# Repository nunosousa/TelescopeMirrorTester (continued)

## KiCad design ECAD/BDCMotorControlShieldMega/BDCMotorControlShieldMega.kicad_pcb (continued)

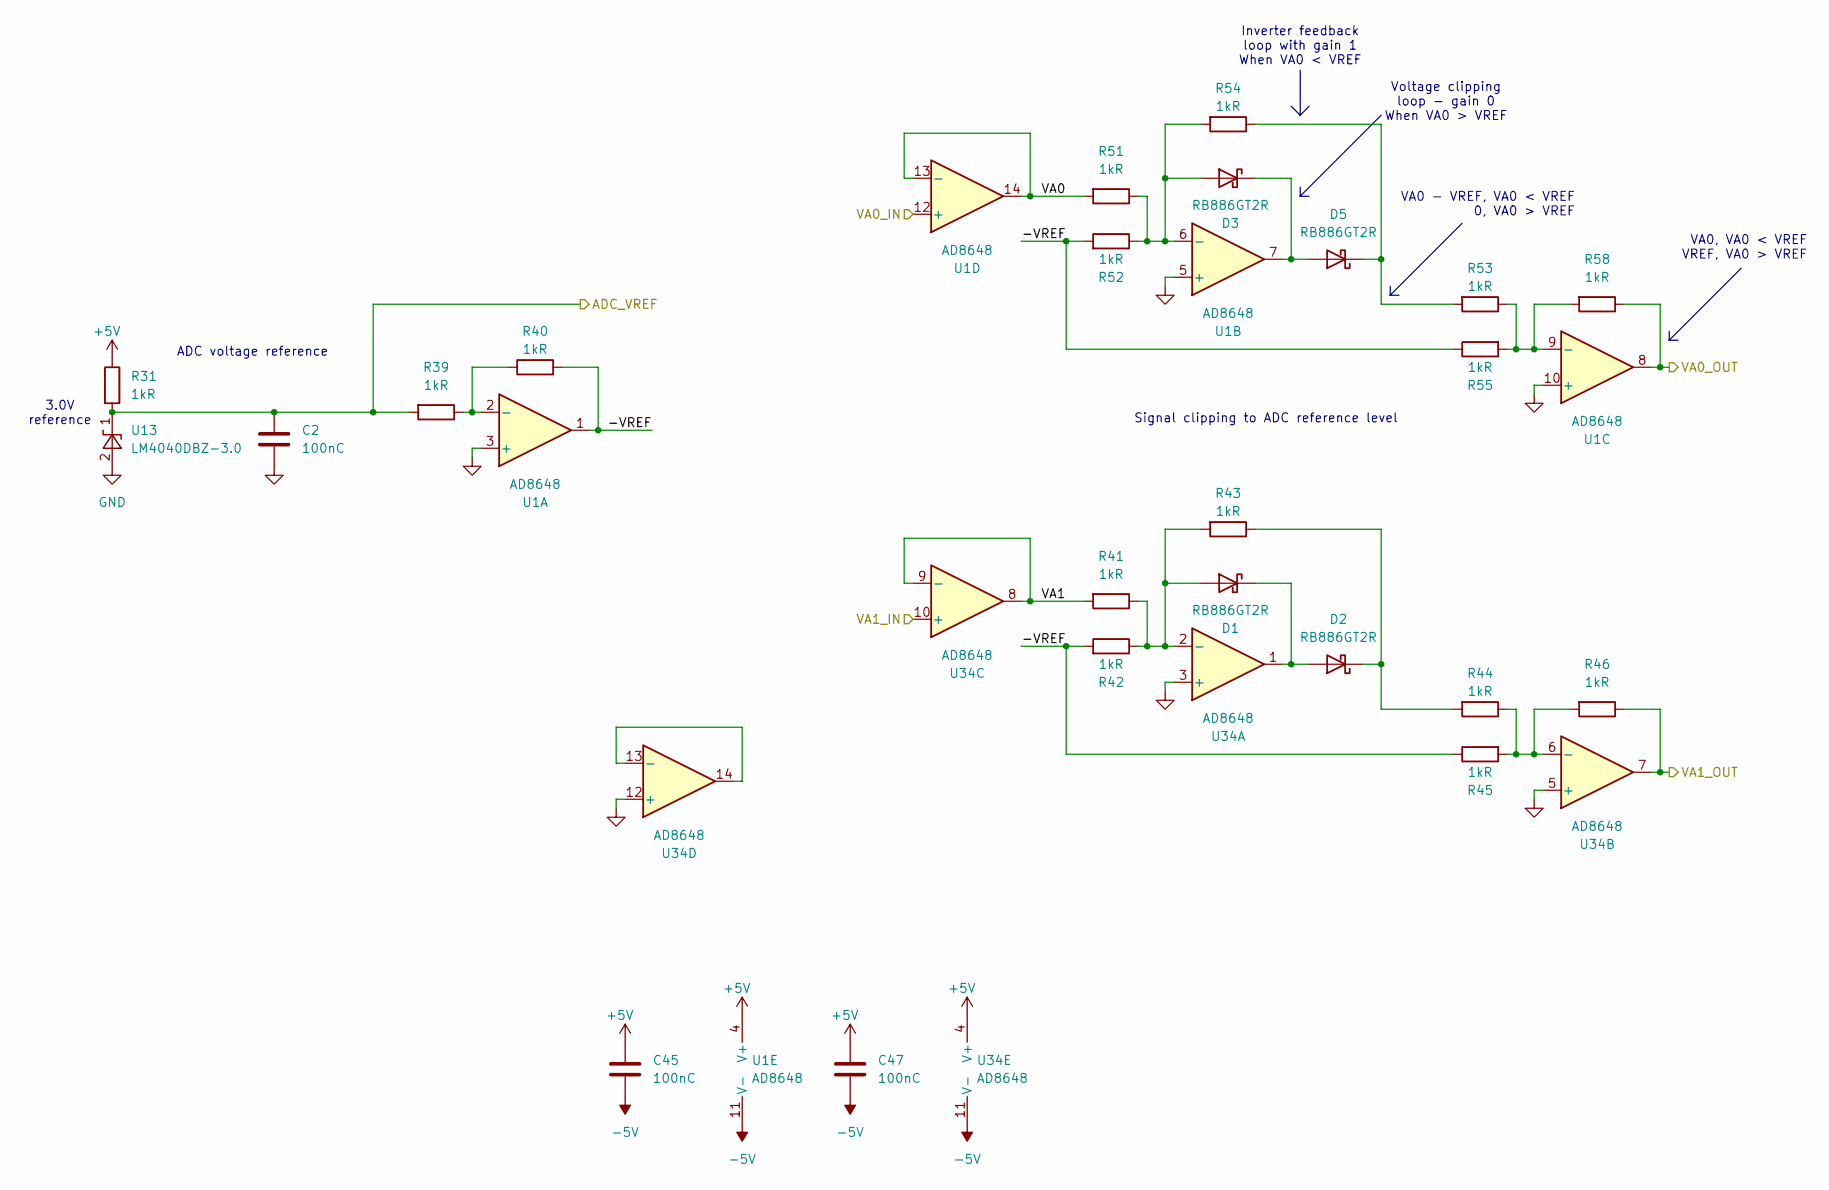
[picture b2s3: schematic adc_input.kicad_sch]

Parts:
C2, C45, C47: 100nC; C_0805_2012Metric
D1, D2, D3, D5: RB886GT2R; MPN RB886GT2R
R31: 1kR; R_0805_2012Metric; MPN AC0805FR-7W1KL
R39, R40, R41, R42, R43, R44, R45, R46, R51, R52, R53, R54, R55, R58: 1kR; R_0805_2012Metric
U1, U34: AD8648; TSSOP-14_4.4x5mm_P0.65mm; MPN AD8648ARUZ
U13: LM4040DBZ-3.0; SOT-23; MPN LM4040B30IDBZR

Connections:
+5V: C45.1, C47.1, R31.1, U1.4 (V+), U34.4 (V+); also elsewhere on the board
-5V: C45.2, C47.2, U1.11 (V-), U34.11 (V-); also elsewhere on the board
/A0: R58.1, U1.8; also elsewhere on the board
/A1: R46.1, U34.7; also elsewhere on the board
/ADC conditioning/-VREF: R40.2, R42.2, R45.1, R52.2, R55.1, U1.1
/ADC conditioning/VA0: R51.2, U1.13 (-), U1.14
/ADC conditioning/VA0_IN: U1.12 (+); also elsewhere on the board
/ADC conditioning/VA1: R41.2, U34.8, U34.9 (-)
/ADC conditioning/VA1_IN: U34.10 (+); also elsewhere on the board
/AREF: C2.1, R31.2, R39.2, U13.1 (K); also elsewhere on the board
GND: C2.2, U1.3 (+), U1.5 (+), U1.10 (+), U13.2 (A), U34.3 (+), U34.5 (+), U34.12 (+); also elsewhere on the board
unnamed: D1.2 (A), R41.1, R42.1, R43.2, U34.2 (-)
unnamed: D1.1 (K), D2.2 (A), U34.1
unnamed: D2.1 (K), R43.1, R44.2
unnamed: D3.2 (A), R51.1, R52.1, R54.2, U1.6 (-)
unnamed: D3.1 (K), D5.2 (A), U1.7
unnamed: D5.1 (K), R53.2, R54.1
unnamed: R39.1, R40.1, U1.2 (-)
unnamed: R53.1, R55.2, R58.2, U1.9 (-)
unnamed: R44.1, R45.2, R46.2, U34.6 (-)
unnamed: U34.13 (-), U34.14

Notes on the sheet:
Inverter feedback loop with gain 1 When VA0 < VREF
3.0V reference
ADC voltage reference
Signal clipping to ADC reference level
Voltage clipping loop - gain 0 When VA0 > VREF
VA0, VA0 < VREF VREF, VA0 > VREF
VA0 - VREF, VA0 < VREF 0, VA0 > VREF

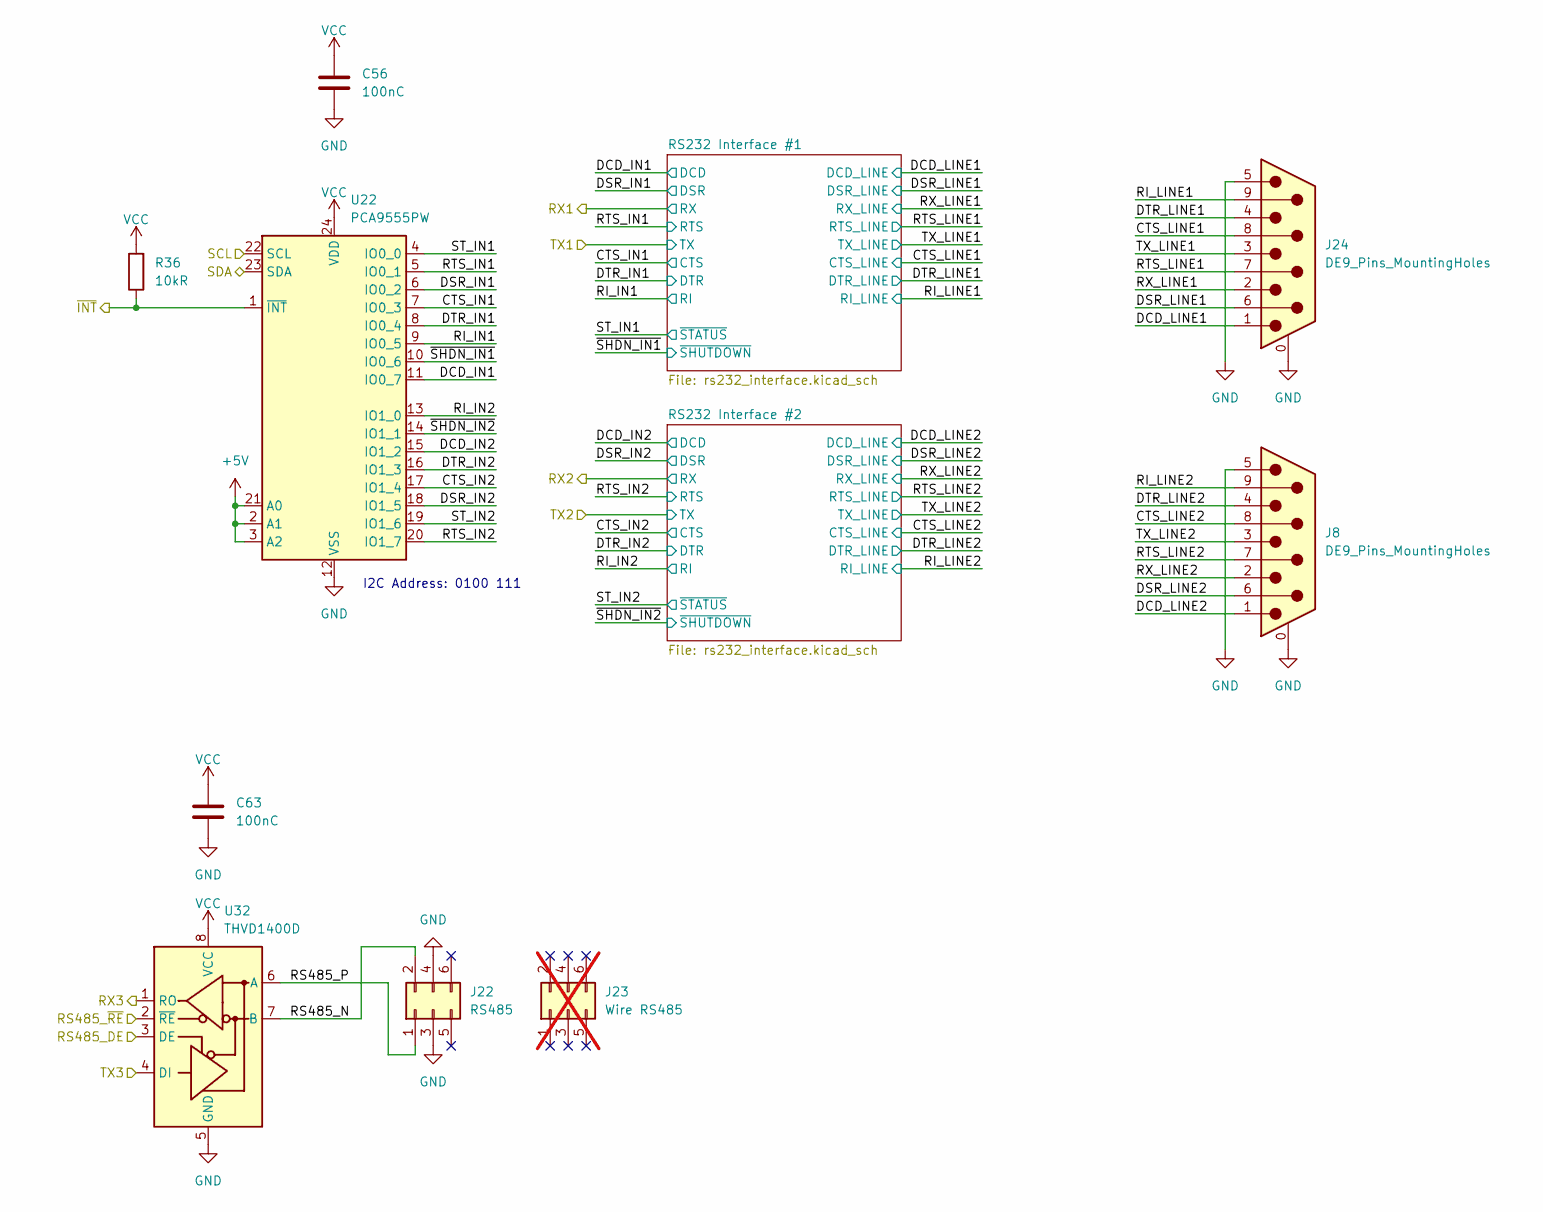
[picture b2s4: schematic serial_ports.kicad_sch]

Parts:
C56, C63: 100nC; C_0805_2012Metric
J8, J24: DE9_Pins_MountingHoles; DSUB-9_Pins_Vertical_P2.77x2.84mm_MountingHoles
J22: RS485; IDC-Header_2x03_P2.54mm_Vertical; MPN HC-JN254-2-03-Z
J23: Wire RS485; IDC-Header_2x03_P2.54mm_Vertical; MPN I254-2*3-G-3-B; not fitted
R36: 10kR; R_0805_2012Metric; MPN RC0805JR-0710KL
U22: PCA9555PW; TSSOP-24_4.4x7.8mm_P0.65mm; MPN PCA9555PW,118
U32: THVD1400D; SOIC-8_3.9x4.9mm_P1.27mm; MPN THVD1400DR

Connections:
+5V: U22.2 (A1), U22.3 (A2), U22.21 (A0); also elsewhere on the board
/*2: U32.2 (~RE); also elsewhere on the board
/*3: U32.3 (DE); also elsewhere on the board
/RX3/15: U32.1 (RO); also elsewhere on the board
/SCL/21: U22.22 (SCL); also elsewhere on the board
/SDA/20: U22.23 (SDA); also elsewhere on the board
/Serial ports/CTS_IN1: U22.7 (IO0_3); also elsewhere on the board
/Serial ports/CTS_IN2: U22.17 (IO1_4); also elsewhere on the board
/Serial ports/CTS_LINE1: J24.8; also elsewhere on the board
/Serial ports/CTS_LINE2: J8.8; also elsewhere on the board
/Serial ports/DCD_IN1: U22.11 (IO0_7); also elsewhere on the board
/Serial ports/DCD_IN2: U22.15 (IO1_2); also elsewhere on the board
/Serial ports/DCD_LINE1: J24.1; also elsewhere on the board
/Serial ports/DCD_LINE2: J8.1; also elsewhere on the board
/Serial ports/DSR_IN1: U22.6 (IO0_2); also elsewhere on the board
/Serial ports/DSR_IN2: U22.18 (IO1_5); also elsewhere on the board
/Serial ports/DSR_LINE1: J24.6; also elsewhere on the board
/Serial ports/DSR_LINE2: J8.6; also elsewhere on the board
/Serial ports/DTR_IN1: U22.8 (IO0_4); also elsewhere on the board
/Serial ports/DTR_IN2: U22.16 (IO1_3); also elsewhere on the board
/Serial ports/DTR_LINE1: J24.4; also elsewhere on the board
/Serial ports/DTR_LINE2: J8.4; also elsewhere on the board
/Serial ports/RI_IN1: U22.9 (IO0_5); also elsewhere on the board
/Serial ports/RI_IN2: U22.13 (IO1_0); also elsewhere on the board
/Serial ports/RI_LINE1: J24.9; also elsewhere on the board
/Serial ports/RI_LINE2: J8.9; also elsewhere on the board
/Serial ports/RS485_N: J22.2, U32.7 (B)
/Serial ports/RS485_P: J22.1, U32.6 (A)
/Serial ports/RTS_IN1: U22.5 (IO0_1); also elsewhere on the board
/Serial ports/RTS_IN2: U22.20 (IO1_7); also elsewhere on the board
/Serial ports/RTS_LINE1: J24.7; also elsewhere on the board
/Serial ports/RTS_LINE2: J8.7; also elsewhere on the board
/Serial ports/RX_LINE1: J24.2; also elsewhere on the board
/Serial ports/RX_LINE2: J8.2; also elsewhere on the board
/Serial ports/ST_IN1: U22.4 (IO0_0); also elsewhere on the board
/Serial ports/ST_IN2: U22.19 (IO1_6); also elsewhere on the board
/Serial ports/TX_LINE1: J24.3; also elsewhere on the board
/Serial ports/TX_LINE2: J8.3; also elsewhere on the board
/Serial ports/~INT: R36.1, U22.1 (~INT)
/Serial ports/~SHDN_IN1: U22.10 (IO0_6); also elsewhere on the board
/Serial ports/~SHDN_IN2: U22.14 (IO1_1); also elsewhere on the board
/TX3/14: U32.4 (DI); also elsewhere on the board
GND: C56.2, C63.2, J8.0 (PAD), J8.5, J22.3, J22.4, J24.0 (PAD), J24.5, U22.12 (VSS), U32.5 (GND); also elsewhere on the board
VCC: C56.1, C63.1, R36.2, U22.24 (VDD), U32.8 (VCC); also elsewhere on the board

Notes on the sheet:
I2C Address: 0100 111

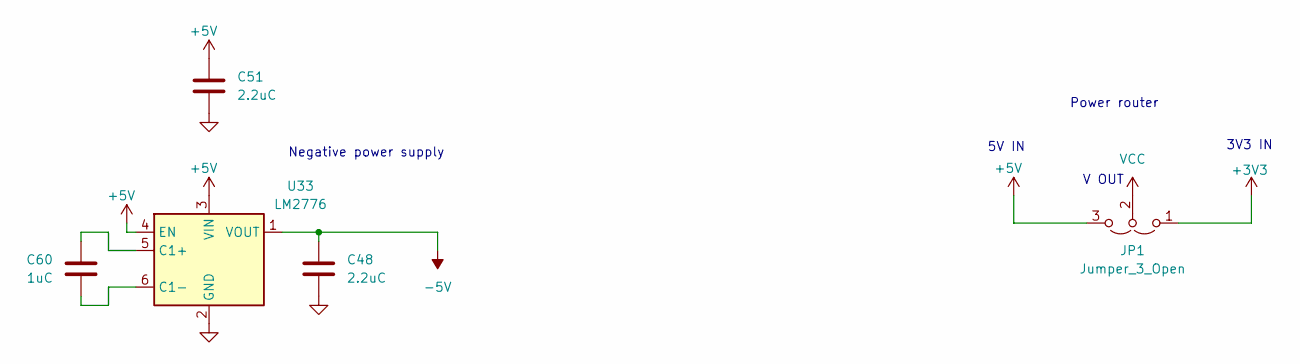
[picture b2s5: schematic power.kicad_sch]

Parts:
C48, C51: 2.2uC; C_0805_2012Metric
C60: 1uC; C_0805_2012Metric
JP1: Jumper_3_Open; PinHeader_1x03_P2.54mm_Vertical
U33: LM2776; SOT-23-6

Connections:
+3V3: JP1.1 (A); also elsewhere on the board
+5V: C51.1, JP1.3 (B), U33.3 (VIN), U33.4 (EN); also elsewhere on the board
-5V: C48.1, U33.1 (VOUT); also elsewhere on the board
GND: C48.2, C51.2, U33.2 (GND); also elsewhere on the board
unnamed: C60.1, U33.5 (C1+)
unnamed: C60.2, U33.6 (C1-)
VCC: JP1.2 (C); also elsewhere on the board

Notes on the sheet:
3V3 IN
Power router
Negative power supply
V OUT
5V IN

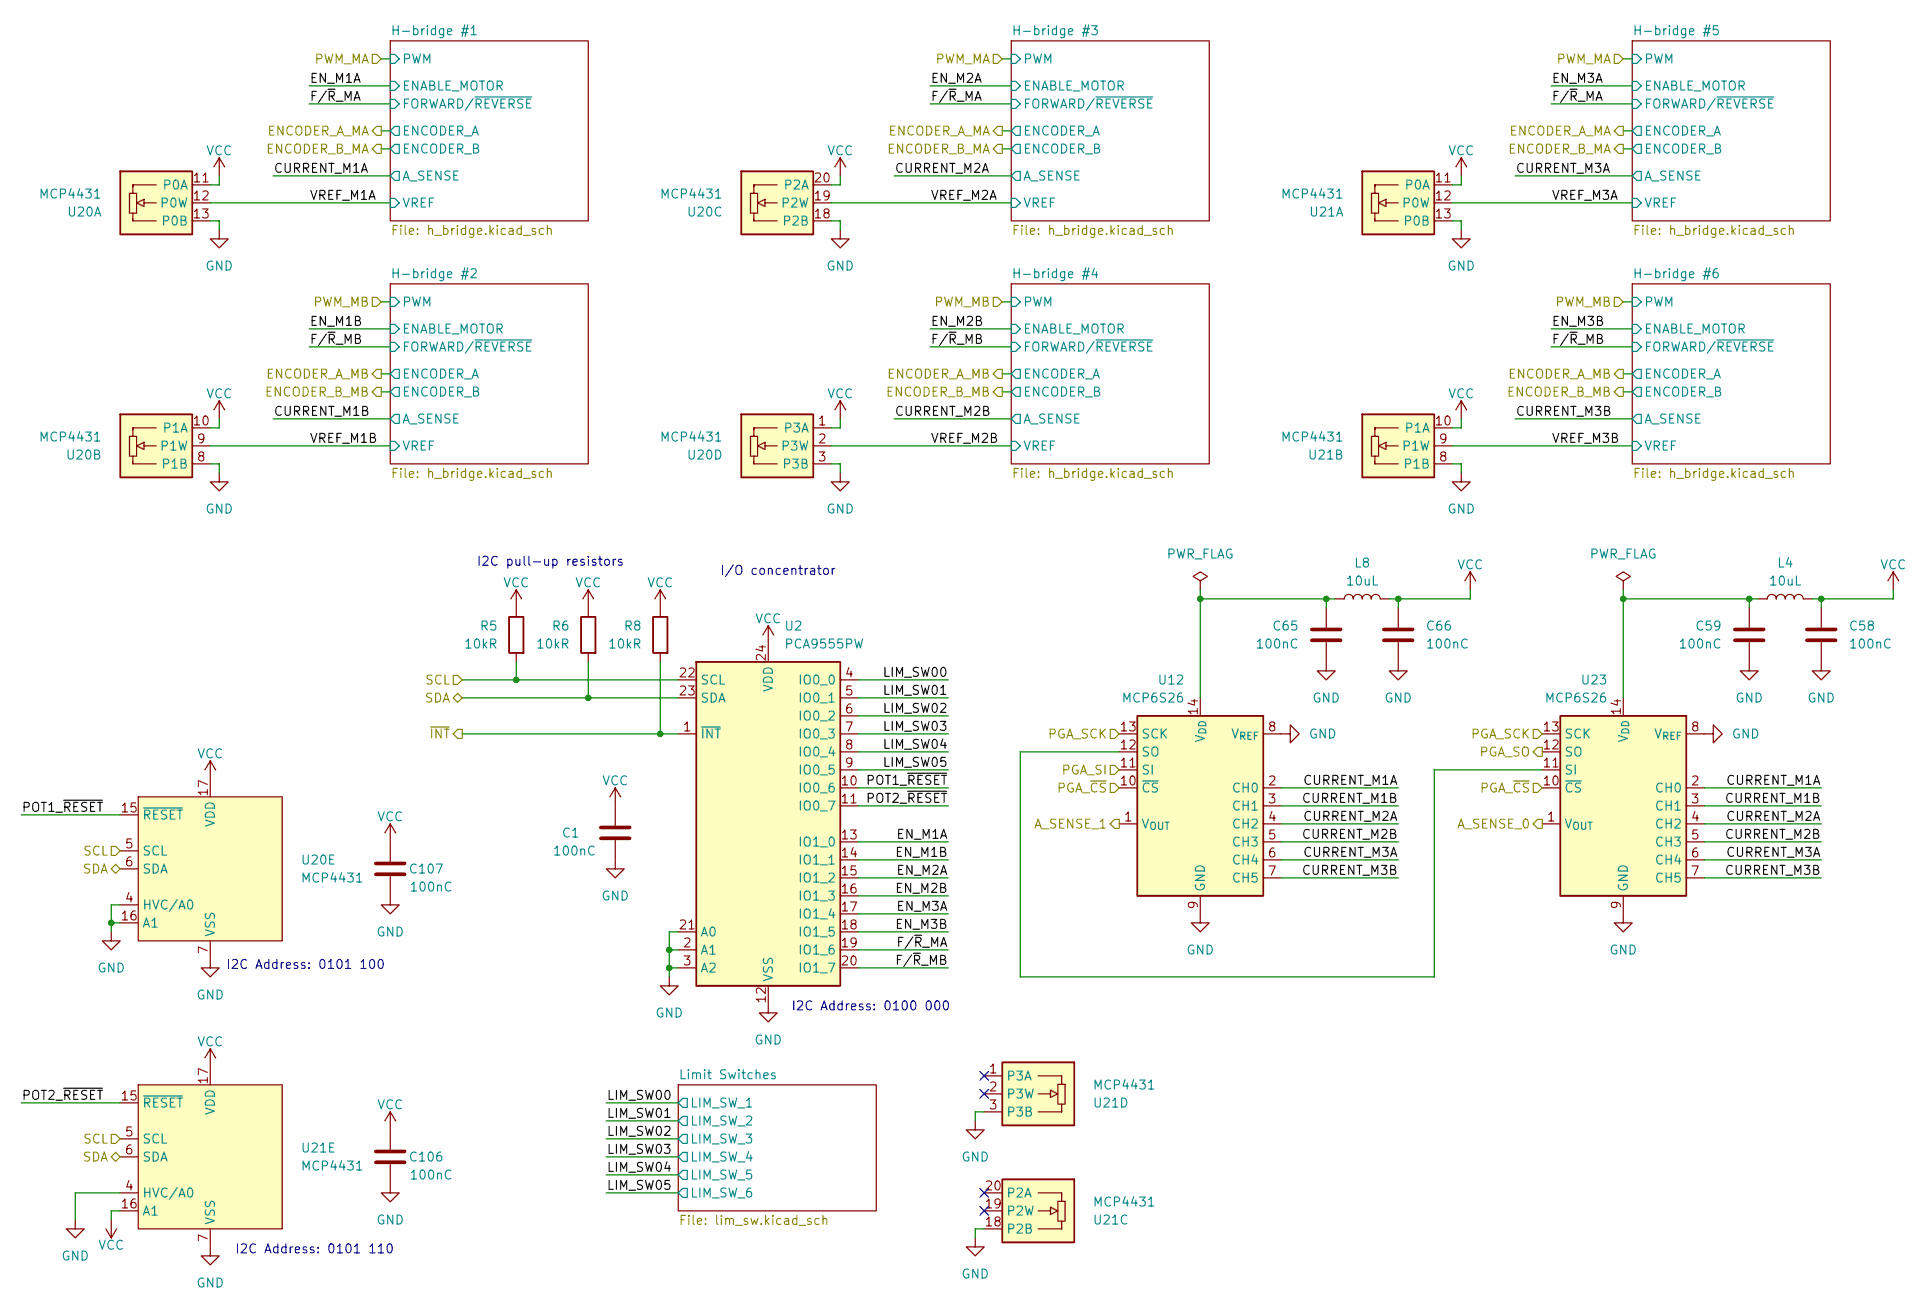
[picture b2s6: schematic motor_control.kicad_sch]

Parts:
C1, C58, C59, C65, C66, C106, C107: 100nC; C_0805_2012Metric
L4, L8: 10uL; L_0805_2012Metric; MPN LQM21FN100M80L
R5, R6, R8: 10kR; R_0805_2012Metric; MPN RC0805JR-0710KL
U2: PCA9555PW; TSSOP-24_4.4x7.8mm_P0.65mm; MPN PCA9555PW,118
U12, U23: MCP6S26; SOIC-14_3.9x8.7mm_P1.27mm; MPN MCP6S26-I/SL
U20, U21: MCP4431; TSSOP-20_4.4x6.5mm_P0.65mm; MPN MCP4431-103E/ST

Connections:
/50: U23.12 (SO); also elsewhere on the board
/51: U12.11 (SI); also elsewhere on the board
/53: U12.10 (~CS), U23.10 (~CS); also elsewhere on the board
/*52: U12.13 (SCK), U23.13 (SCK); also elsewhere on the board
/ADC conditioning/VA0_IN: U23.1 (V_{OUT}); also elsewhere on the board
/ADC conditioning/VA1_IN: U12.1 (V_{OUT}); also elsewhere on the board
/Motor Control/CURRENT_M1A: U12.2 (CH0), U23.2 (CH0); also elsewhere on the board
/Motor Control/CURRENT_M1B: U12.3 (CH1), U23.3 (CH1); also elsewhere on the board
/Motor Control/CURRENT_M2A: U12.4 (CH2), U23.4 (CH2); also elsewhere on the board
/Motor Control/CURRENT_M2B: U12.5 (CH3), U23.5 (CH3); also elsewhere on the board
/Motor Control/CURRENT_M3A: U12.6 (CH4), U23.6 (CH4); also elsewhere on the board
/Motor Control/CURRENT_M3B: U12.7 (CH5), U23.7 (CH5); also elsewhere on the board
/Motor Control/EN_M1A: U2.13 (IO1_0); also elsewhere on the board
/Motor Control/EN_M1B: U2.14 (IO1_1); also elsewhere on the board
/Motor Control/EN_M2A: U2.15 (IO1_2); also elsewhere on the board
/Motor Control/EN_M2B: U2.16 (IO1_3); also elsewhere on the board
/Motor Control/EN_M3A: U2.17 (IO1_4); also elsewhere on the board
/Motor Control/EN_M3B: U2.18 (IO1_5); also elsewhere on the board
/Motor Control/F/~R_MA: U2.19 (IO1_6); also elsewhere on the board
/Motor Control/F/~R_MB: U2.20 (IO1_7); also elsewhere on the board
/Motor Control/LIM_SW00: U2.4 (IO0_0); also elsewhere on the board
/Motor Control/LIM_SW01: U2.5 (IO0_1); also elsewhere on the board
/Motor Control/LIM_SW02: U2.6 (IO0_2); also elsewhere on the board
/Motor Control/LIM_SW03: U2.7 (IO0_3); also elsewhere on the board
/Motor Control/LIM_SW04: U2.8 (IO0_4); also elsewhere on the board
/Motor Control/LIM_SW05: U2.9 (IO0_5); also elsewhere on the board
/Motor Control/POT1_~RESET: U2.10 (IO0_6), U20.15 (~RESET)
/Motor Control/POT2_~RESET: U2.11 (IO0_7), U21.15 (~RESET)
/Motor Control/VREF_M1A: U20.12 (P0W); also elsewhere on the board
/Motor Control/VREF_M1B: U20.9 (P1W); also elsewhere on the board
/Motor Control/VREF_M2A: U20.19 (P2W); also elsewhere on the board
/Motor Control/VREF_M2B: U20.2 (P3W); also elsewhere on the board
/Motor Control/VREF_M3A: U21.12 (P0W); also elsewhere on the board
/Motor Control/VREF_M3B: U21.9 (P1W); also elsewhere on the board
/Motor Control/~INT: R8.2, U2.1 (~INT)
/SCL/21: R5.2, U2.22 (SCL), U20.5 (SCL), U21.5 (SCL); also elsewhere on the board
/SDA/20: R6.2, U2.23 (SDA), U20.6 (SDA), U21.6 (SDA); also elsewhere on the board
GND: C1.2, C58.2, C59.2, C65.2, C66.2, C106.2, C107.2, U2.2 (A1), U2.3 (A2), U2.12 (VSS), U2.21 (A0), U12.8 (V_{REF}), U12.9 (GND), U20.3 (P3B), U20.4 (HVC/A0), U20.7 (VSS), U20.8 (P1B), U20.13 (P0B), U20.16 (A1), U20.18 (P2B), U21.3 (P3B), U21.4 (HVC/A0), U21.7 (VSS), U21.8 (P1B), U21.13 (P0B), U21.18 (P2B), U23.8 (V_{REF}), U23.9 (GND); also elsewhere on the board
unnamed: U12.12 (SO), U23.11 (SI)
unnamed: C65.1, L8.2, U12.14 (V_{DD})
unnamed: C59.1, L4.2, U23.14 (V_{DD})
VCC: C1.1, C58.1, C66.1, C106.1, C107.1, L4.1, L8.1, R5.1, R6.1, R8.1, U2.24 (VDD), U20.1 (P3A), U20.10 (P1A), U20.11 (P0A), U20.17 (VDD), U20.20 (P2A), U21.10 (P1A), U21.11 (P0A), U21.16 (A1), U21.17 (VDD); also elsewhere on the board

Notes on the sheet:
I2C pull-up resistors
I2C Address: 0100 000
I2C Address: 0101 100
I/O concentrator
I2C Address: 0101 110

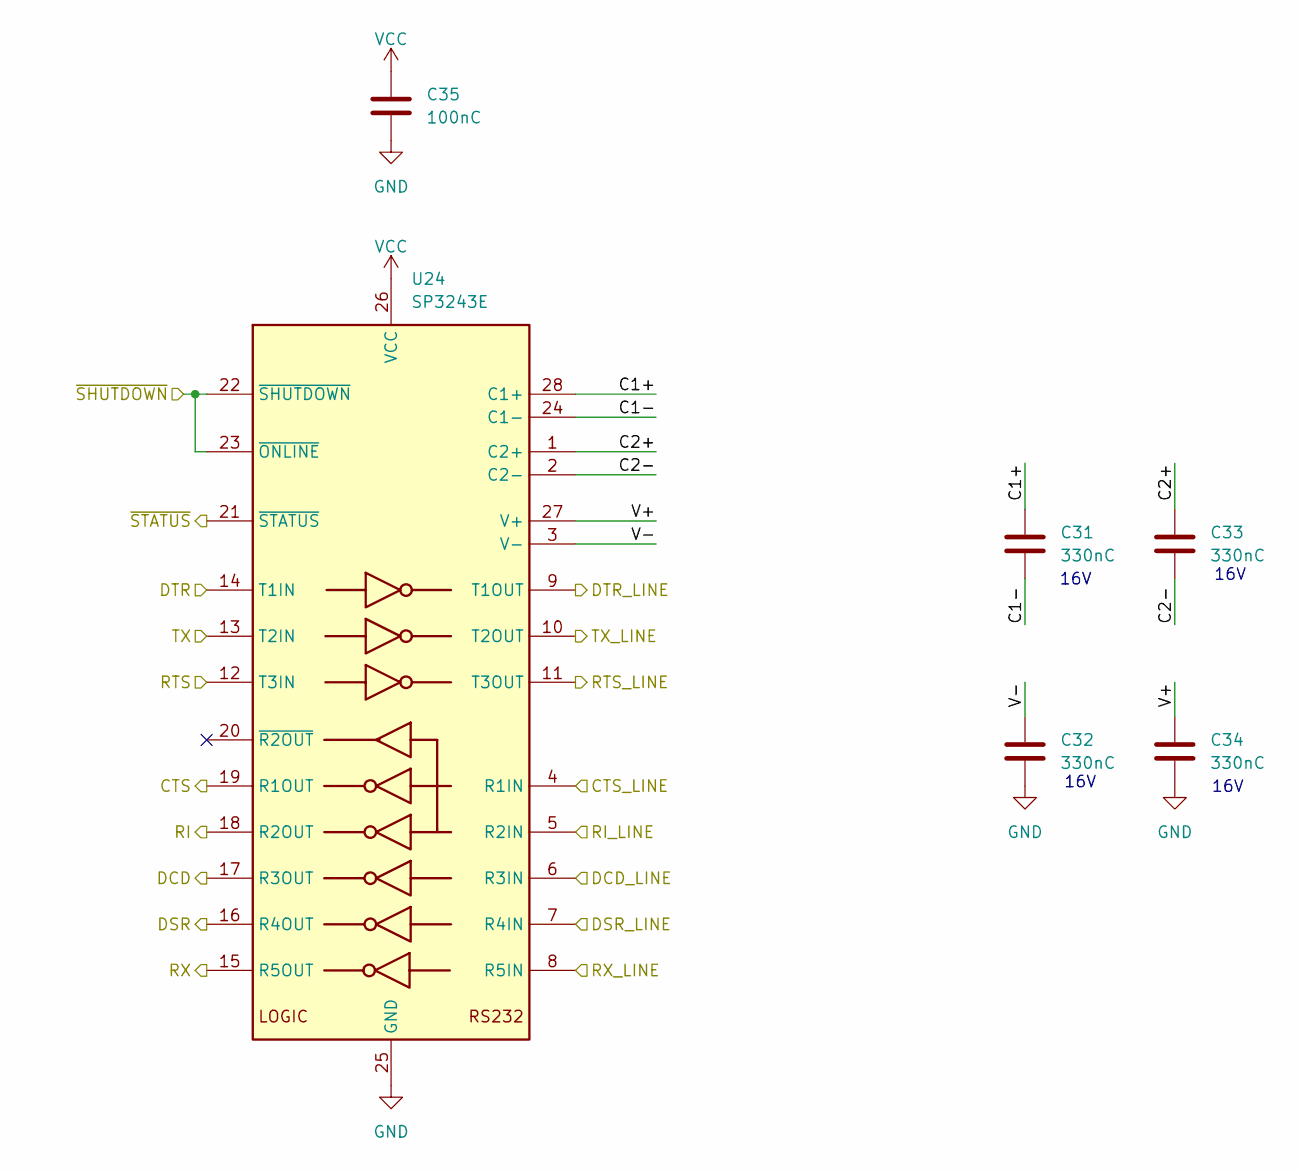
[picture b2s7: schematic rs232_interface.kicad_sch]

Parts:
C31, C32, C33, C34: 330nC; C_0805_2012Metric
C35: 100nC; C_0805_2012Metric
U24: SP3243E; TSSOP-28_4.4x9.7mm_P0.65mm; MPN SP3243EBEY-L/TR

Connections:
/RX1/19: U24.15 (R5OUT); also elsewhere on the board
/Serial ports/CTS_IN1: U24.19 (R1OUT); also elsewhere on the board
/Serial ports/CTS_LINE1: U24.4 (R1IN); also elsewhere on the board
/Serial ports/DCD_IN1: U24.17 (R3OUT); also elsewhere on the board
/Serial ports/DCD_LINE1: U24.6 (R3IN); also elsewhere on the board
/Serial ports/DSR_IN1: U24.16 (R4OUT); also elsewhere on the board
/Serial ports/DSR_LINE1: U24.7 (R4IN); also elsewhere on the board
/Serial ports/DTR_IN1: U24.14 (T1IN); also elsewhere on the board
/Serial ports/DTR_LINE1: U24.9 (T1OUT); also elsewhere on the board
/Serial ports/RI_IN1: U24.18 (R2OUT); also elsewhere on the board
/Serial ports/RI_LINE1: U24.5 (R2IN); also elsewhere on the board
/Serial ports/RS232 Interface #1/C1+: C31.1, U24.28 (C1+)
/Serial ports/RS232 Interface #1/C1-: C31.2, U24.24 (C1-)
/Serial ports/RS232 Interface #1/C2+: C33.1, U24.1 (C2+)
/Serial ports/RS232 Interface #1/C2-: C33.2, U24.2 (C2-)
/Serial ports/RS232 Interface #1/V+: C34.1, U24.27 (V+)
/Serial ports/RS232 Interface #1/V-: C32.1, U24.3 (V-)
/Serial ports/RTS_IN1: U24.12 (T3IN); also elsewhere on the board
/Serial ports/RTS_LINE1: U24.11 (T3OUT); also elsewhere on the board
/Serial ports/RX_LINE1: U24.8 (R5IN); also elsewhere on the board
/Serial ports/ST_IN1: U24.21 (~STATUS); also elsewhere on the board
/Serial ports/TX_LINE1: U24.10 (T2OUT); also elsewhere on the board
/Serial ports/~SHDN_IN1: U24.22 (~SHUTDOWN), U24.23 (~ONLINE); also elsewhere on the board
/TX1/18: U24.13 (T2IN); also elsewhere on the board
GND: C32.2, C34.2, C35.2, U24.25 (GND); also elsewhere on the board
VCC: C35.1, U24.26 (VCC); also elsewhere on the board

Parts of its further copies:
C36, C37, C38, C39: 330nC; C_0805_2012Metric
C40: 100nC; C_0805_2012Metric
U31: SP3243E; TSSOP-28_4.4x9.7mm_P0.65mm; MPN SP3243EBEY-L/TR

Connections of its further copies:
/RX2/17: U31.15 (R5OUT); also elsewhere on the board
/Serial ports/CTS_IN2: U31.19 (R1OUT); also elsewhere on the board
/Serial ports/CTS_LINE2: U31.4 (R1IN); also elsewhere on the board
/Serial ports/DCD_IN2: U31.17 (R3OUT); also elsewhere on the board
/Serial ports/DCD_LINE2: U31.6 (R3IN); also elsewhere on the board
/Serial ports/DSR_IN2: U31.16 (R4OUT); also elsewhere on the board
/Serial ports/DSR_LINE2: U31.7 (R4IN); also elsewhere on the board
/Serial ports/DTR_IN2: U31.14 (T1IN); also elsewhere on the board
/Serial ports/DTR_LINE2: U31.9 (T1OUT); also elsewhere on the board
/Serial ports/RI_IN2: U31.18 (R2OUT); also elsewhere on the board
/Serial ports/RI_LINE2: U31.5 (R2IN); also elsewhere on the board
/Serial ports/RS232 Interface #2/C1+: C36.1, U31.28 (C1+)
/Serial ports/RS232 Interface #2/C1-: C36.2, U31.24 (C1-)
/Serial ports/RS232 Interface #2/C2+: C38.1, U31.1 (C2+)
/Serial ports/RS232 Interface #2/C2-: C38.2, U31.2 (C2-)
/Serial ports/RS232 Interface #2/V+: C39.1, U31.27 (V+)
/Serial ports/RS232 Interface #2/V-: C37.1, U31.3 (V-)
/Serial ports/RTS_IN2: U31.12 (T3IN); also elsewhere on the board
/Serial ports/RTS_LINE2: U31.11 (T3OUT); also elsewhere on the board
/Serial ports/RX_LINE2: U31.8 (R5IN); also elsewhere on the board
/Serial ports/ST_IN2: U31.21 (~STATUS); also elsewhere on the board
/Serial ports/TX_LINE2: U31.10 (T2OUT); also elsewhere on the board
/Serial ports/~SHDN_IN2: U31.22 (~SHUTDOWN), U31.23 (~ONLINE); also elsewhere on the board
/TX2/16: U31.13 (T2IN); also elsewhere on the board
GND: C37.2, C39.2, C40.2, U31.25 (GND); also elsewhere on the board
VCC: C40.1, U31.26 (VCC); also elsewhere on the board

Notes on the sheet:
16V
